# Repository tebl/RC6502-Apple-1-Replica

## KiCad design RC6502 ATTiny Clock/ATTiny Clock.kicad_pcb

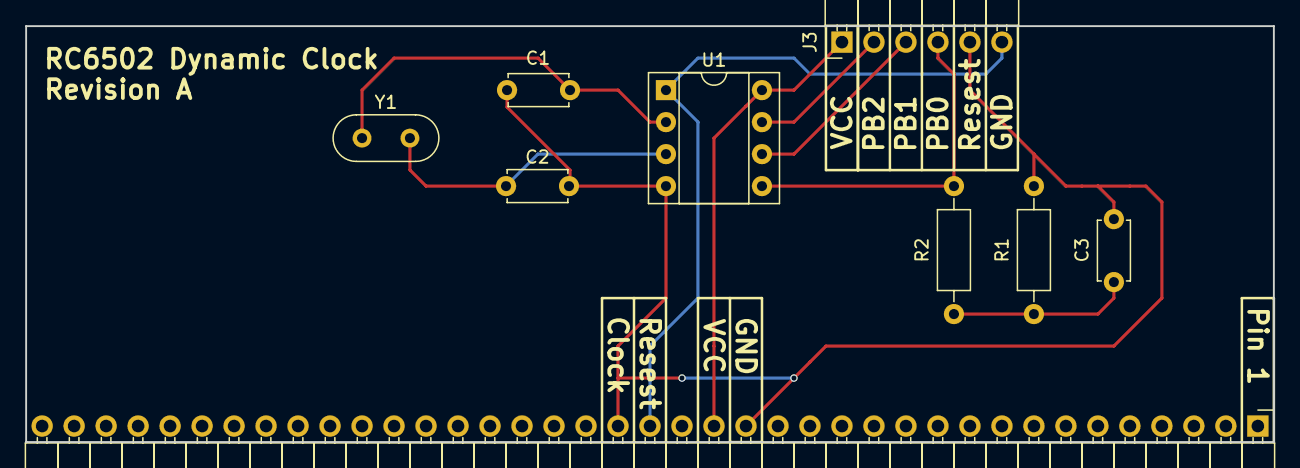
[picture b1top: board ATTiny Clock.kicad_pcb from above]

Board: 2 copper layers, 99.1 x 33.0 mm, 9 parts (0 on the bottom side), 9 nets.

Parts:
C1, C2: 22pF; C_Disc_D4.7mm_W2.5mm_P5.00mm
C3: 0.1uF; C_Disc_D4.7mm_W2.5mm_P5.00mm
J1: CONN_01X39; Pin_Header_Angled_1x39_Pitch2.54mm
J3: CONN_01X06; Pin_Header_Angled_1x06_Pitch2.54mm
R1: 10k; R_Axial_DIN0207_L6.3mm_D2.5mm_P10.16mm_Horizontal
R2: 1k; R_Axial_DIN0207_L6.3mm_D2.5mm_P10.16mm_Horizontal
U1: ATTINY85-20PU; DIP-8_W7.62mm_Socket
Y1: 20Mhz; Crystal_HC52-6mm_Vertical

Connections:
CLOCK: C1.2, C2.2, C3.2, J1.17, J1.21, J3.5, R1.2, U1.4
unnamed: C3.1, R1.1, R2.2
PB0: J3.4, R2.1, U1.5
PB1: J3.3, U1.6
PB2: J3.2, U1.7
RESET: J1.20, J3.6, U1.1
Vcc: J1.18, J3.1, U1.8
XTAL1: C1.1, U1.2, Y1.1
XTAL2: C2.1, U1.3, Y1.2

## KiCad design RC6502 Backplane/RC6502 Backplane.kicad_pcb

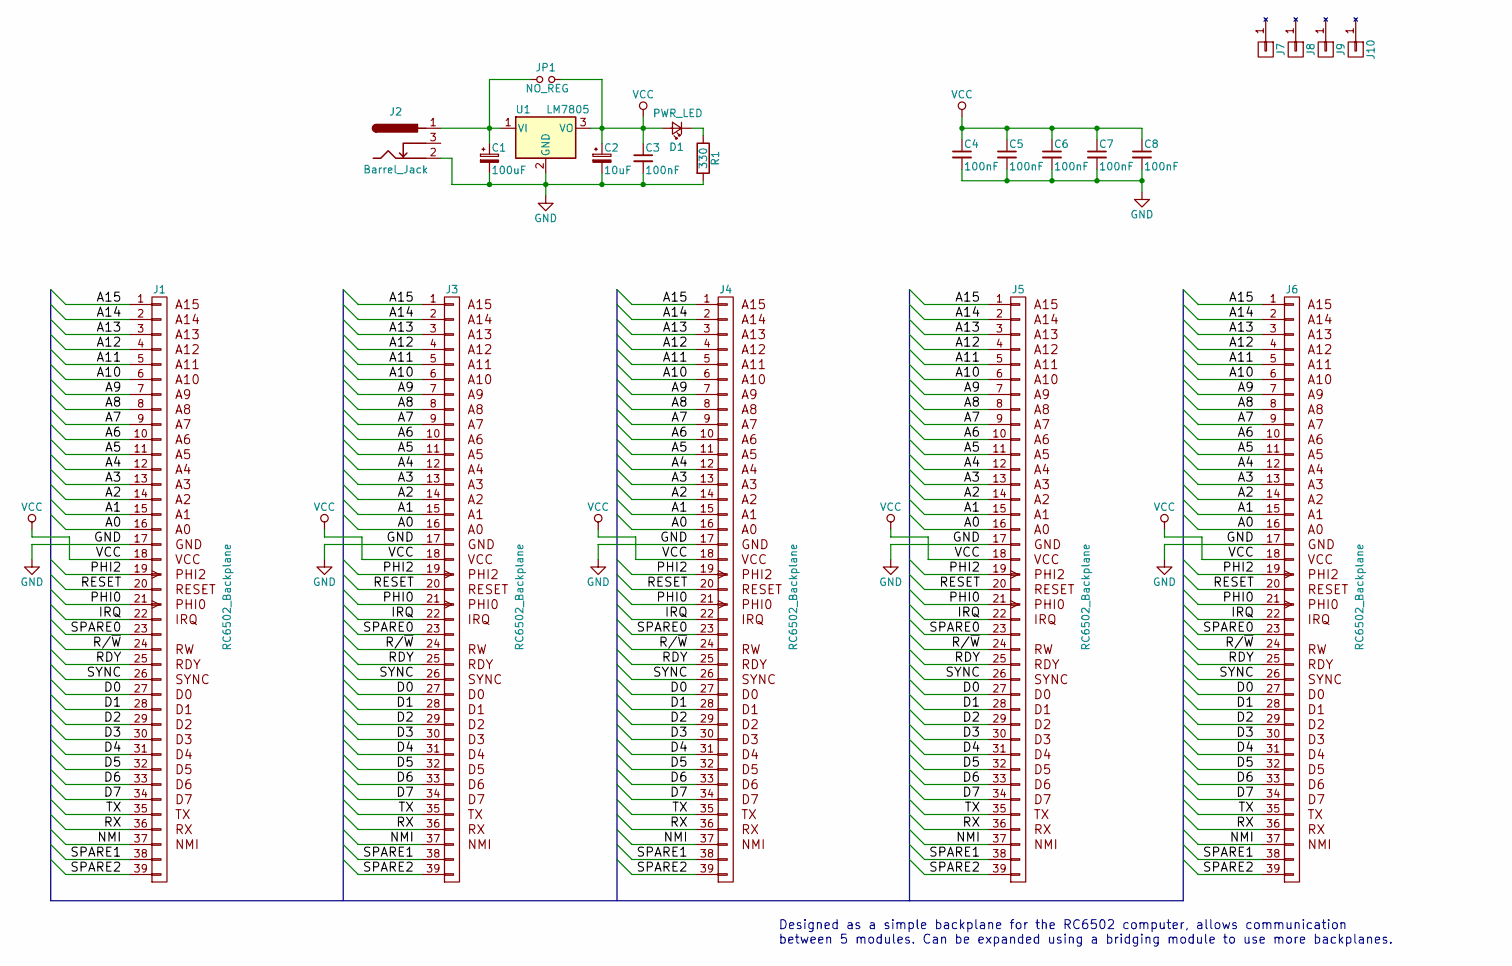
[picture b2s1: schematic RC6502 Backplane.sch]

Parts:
C1: 100uF; CP_Radial_D5.0mm_P2.50mm
C2: 10uF; CP_Radial_D4.0mm_P2.00mm
C3, C4, C5, C6, C7, C8: 100nF; C_Disc_D4.7mm_W2.5mm_P5.00mm
D1: PWR_LED; LED_D5.0mm
J1, J3, J4, J5, J6: RC6502_Backplane; Pin_Header_Straight_1x39_Pitch2.54mm
J2: Barrel_Jack; BARREL_JACK
J7, J8, J9, J10: Mounting
JP1: NO_REG; Pin_Header_Straight_1x02_Pitch2.54mm
R1: 330; R_Axial_DIN0207_L6.3mm_D2.5mm_P10.16mm_Horizontal
U1: LM7805; TO-220-3_Horizontal

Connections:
/A0: J1.16 (A0), J3.16 (A0), J4.16 (A0), J5.16 (A0), J6.16 (A0)
/A1: J1.15 (A1), J3.15 (A1), J4.15 (A1), J5.15 (A1), J6.15 (A1)
/A2: J1.14 (A2), J3.14 (A2), J4.14 (A2), J5.14 (A2), J6.14 (A2)
/A3: J1.13 (A3), J3.13 (A3), J4.13 (A3), J5.13 (A3), J6.13 (A3)
/A4: J1.12 (A4), J3.12 (A4), J4.12 (A4), J5.12 (A4), J6.12 (A4)
/A5: J1.11 (A5), J3.11 (A5), J4.11 (A5), J5.11 (A5), J6.11 (A5)
/A6: J1.10 (A6), J3.10 (A6), J4.10 (A6), J5.10 (A6), J6.10 (A6)
/A7: J1.9 (A7), J3.9 (A7), J4.9 (A7), J5.9 (A7), J6.9 (A7)
/A8: J1.8 (A8), J3.8 (A8), J4.8 (A8), J5.8 (A8), J6.8 (A8)
/A9: J1.7 (A9), J3.7 (A9), J4.7 (A9), J5.7 (A9), J6.7 (A9)
/A10: J1.6 (A10), J3.6 (A10), J4.6 (A10), J5.6 (A10), J6.6 (A10)
/A11: J1.5 (A11), J3.5 (A11), J4.5 (A11), J5.5 (A11), J6.5 (A11)
/A12: J1.4 (A12), J3.4 (A12), J4.4 (A12), J5.4 (A12), J6.4 (A12)
/A13: J1.3 (A13), J3.3 (A13), J4.3 (A13), J5.3 (A13), J6.3 (A13)
/A14: J1.2 (A14), J3.2 (A14), J4.2 (A14), J5.2 (A14), J6.2 (A14)
/A15: J1.1 (A15), J3.1 (A15), J4.1 (A15), J5.1 (A15), J6.1 (A15)
/D0: J1.27 (D0), J3.27 (D0), J4.27 (D0), J5.27 (D0), J6.27 (D0)
/D1: J1.28 (D1), J3.28 (D1), J4.28 (D1), J5.28 (D1), J6.28 (D1)
/D2: J1.29 (D2), J3.29 (D2), J4.29 (D2), J5.29 (D2), J6.29 (D2)
/D3: J1.30 (D3), J3.30 (D3), J4.30 (D3), J5.30 (D3), J6.30 (D3)
/D4: J1.31 (D4), J3.31 (D4), J4.31 (D4), J5.31 (D4), J6.31 (D4)
/D5: J1.32 (D5), J3.32 (D5), J4.32 (D5), J5.32 (D5), J6.32 (D5)
/D6: J1.33 (D6), J3.33 (D6), J4.33 (D6), J5.33 (D6), J6.33 (D6)
/D7: J1.34 (D7), J3.34 (D7), J4.34 (D7), J5.34 (D7), J6.34 (D7)
/IRQ: J1.22 (IRQ), J3.22 (IRQ), J4.22 (IRQ), J5.22 (IRQ), J6.22 (IRQ)
/NMI: J1.37 (NMI), J3.37 (NMI), J4.37 (NMI), J5.37 (NMI), J6.37 (NMI)
/PHI0: J1.21 (PHI0), J3.21 (PHI0), J4.21 (PHI0), J5.21 (PHI0), J6.21 (PHI0)
/PHI2: J1.19 (PHI2), J3.19 (PHI2), J4.19 (PHI2), J5.19 (PHI2), J6.19 (PHI2)
/R/~W: J1.24 (RW), J3.24 (RW), J4.24 (RW), J5.24 (RW), J6.24 (RW)
/RDY: J1.25 (READY), J3.25 (READY), J4.25 (READY), J5.25 (READY), J6.25 (READY)
/RESET: J1.20 (RESET), J3.20 (RESET), J4.20 (RESET), J5.20 (RESET), J6.20 (RESET)
/RX: J1.36 (RX), J3.36 (RX), J4.36 (RX), J5.36 (RX), J6.36 (RX)
/SPARE0: J1.23, J3.23, J4.23, J5.23, J6.23
/SPARE1: J1.38, J3.38, J4.38, J5.38, J6.38
/SPARE2: J1.39, J3.39, J4.39, J5.39, J6.39
/SYNC: J1.26 (SYNC), J3.26 (SYNC), J4.26 (SYNC), J5.26 (SYNC), J6.26 (SYNC)
/TX: J1.35 (TX), J3.35 (TX), J4.35 (TX), J5.35 (TX), J6.35 (TX)
GND: C1.2, C2.2, C3.2, C4.2, C5.2, C6.2, C7.2, C8.2, J1.17, J2.2, J3.17, J4.17, J5.17, J6.17, R1.2, U1.2 (GND)
unnamed: C1.1, J2.1, JP1.1, U1.1 (VI)
unnamed: D1.1 (K), R1.1
VCC: C2.1, C3.1, C4.1, C5.1, C6.1, C7.1, C8.1, D1.2 (A), J1.18, J3.18, J4.18, J5.18, J6.18, JP1.2, U1.3 (VO)

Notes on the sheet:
Designed as a simple backplane for the RC6502 computer, allows communication between 5 modules. Can be expanded using a bridging module to use more backplanes.

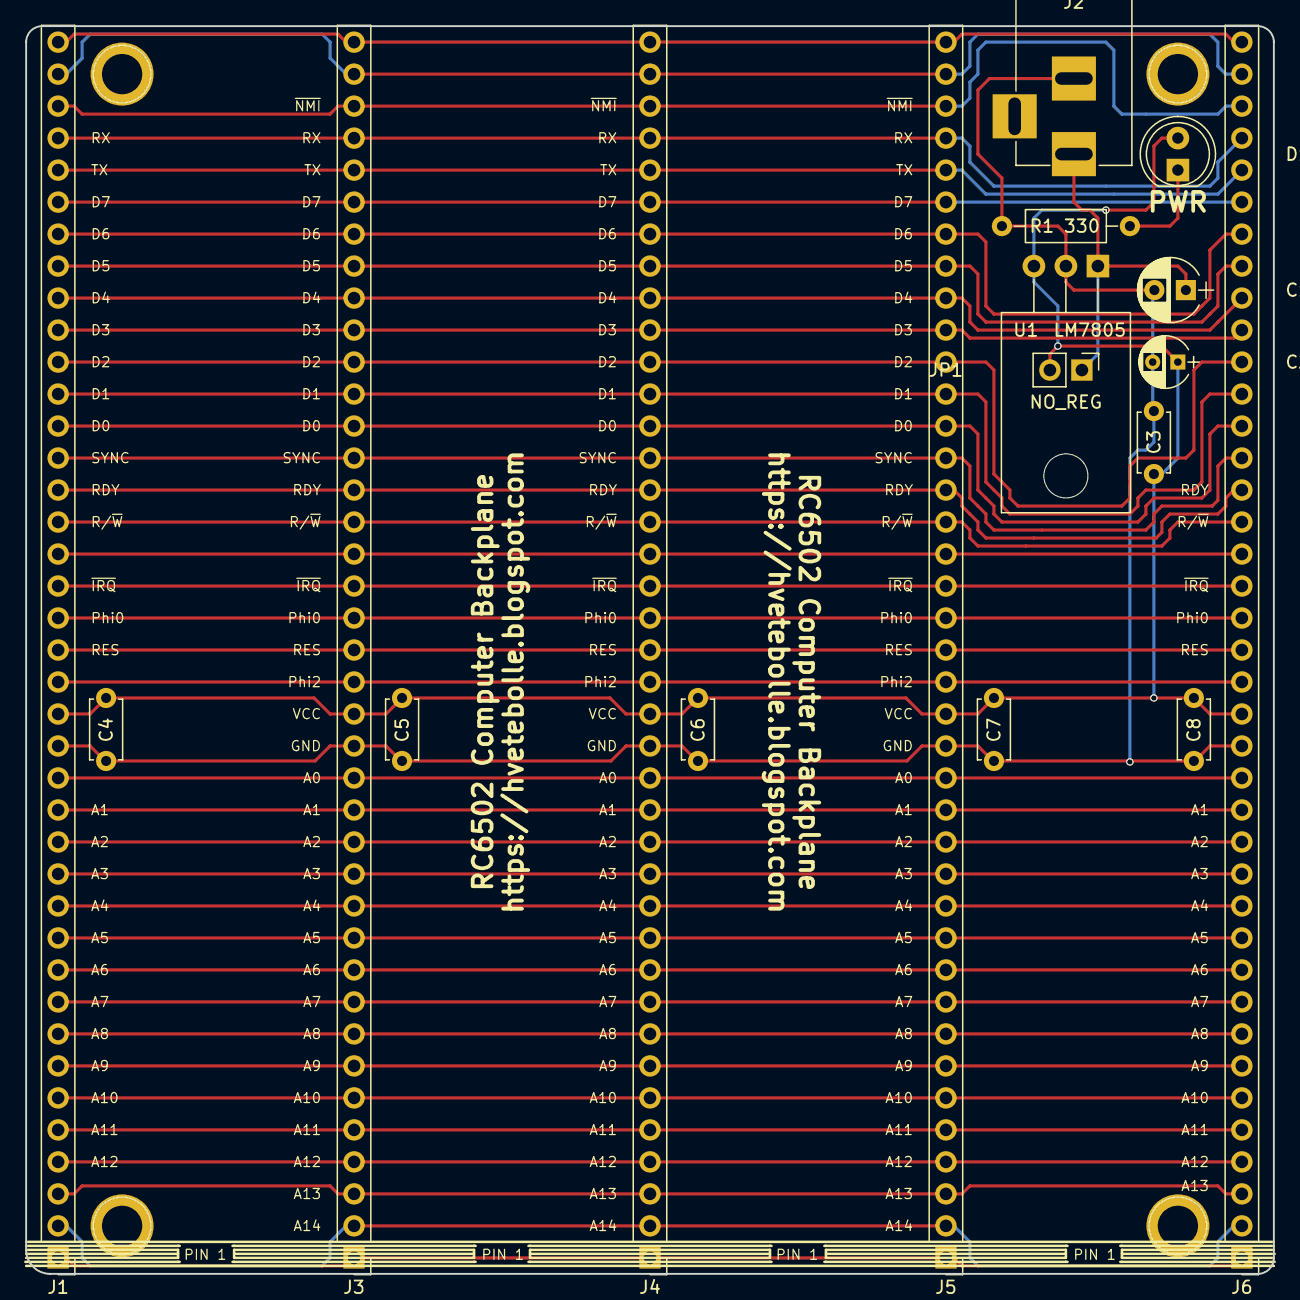
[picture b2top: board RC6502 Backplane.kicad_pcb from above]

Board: 2 copper layers, 99.1 x 99.1 mm, 22 parts (0 on the bottom side), 41 nets.

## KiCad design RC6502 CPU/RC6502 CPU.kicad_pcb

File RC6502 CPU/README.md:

# RC6502 CPU

Ah... The CPU-module (Central Processing Unit), definitely the brains of the operation! While the original sported an MOS-branded, the same company later bought out by Commodore and adapter for their computers, ceramic 6502 CPU the later clones available to us now haven't changed all that much. For that reason you can easily substitute the MOS-part with an easily obtainable UM6502 or an SY6502 without any changes, the newer and substantially changed W65C02 however remains incompatible at the moment.

The original computer ran at a blazing 1Mhz, but if you can find a 6502A you could probably crank this computer all the way up to 2Mhz! The speed the computer would run at (successfully or not) will be determined by the crystal oscillator, while it can be mounted onto the CPU-module and enabled by jumpering JP1/JP2 the logical place for this in a more modern configuration would be on the [Reset circuit](https://github.com/tebl/RC6502-Apple-1-Replica/tree/master/RC6502%20Reset%20Circuit)-module. The reason for including it here is simply that the original Apple 1 computer didn't have a power-on reset circuitry, but seriously - get one! If you have plans for building more than one CPU boards with varying speeds, it would make sense to keep these together on the same board so that you can easily swap between them.

Revision A of the board is shown below, the newer revisions have a more simplified design due to a separate RD-signal being dropped from later designs. This was originally intended to help compatibility with the RC2014 computer, but this idea was abandoned due to the required increase in complexity in order to support a handfull of builds.

# Schematic
The supplied KiCad files should be sufficient as both a schematic and as a starting
point for ordering PCBs, the schematic is also available in
[PDF-format](https://github.com/tebl/RC6502-Apple-1-Replica/raw/master/RC6502%20CPU/export/RC6502%20CPU.pdf). You can refer to the BOM below for a list of suggested components to use, part numbers in parenthesis are optional and is not required.

# BOM
These are the components needed to put together your very own ROM-module for the RC6502 computer, should be able to get all of this from your favourite parts supplier through your favourite local parts supplier. For the pin headers, both male and female - if you can't find the exact pin count, just buy the longer versions and snip/cut off the parts you don't need (get extra in case of accidents, and don't cut yourself either!). As previously mentioned, part counts in parenthesis are to be considered optional so feel free to leave them out if you don't have any specific plans for them.

| Reference | Item                                  | Count  |
| --------- | ------------------------------------- | ------ |
| PCB       | Fabricate yourself using KiCad files  |     1  |
| U1        | 6502 CPU DIP-40, UM6502 or SY6502     |     1  |
| J1        | 1x39 right angle pin header, male     |     1  |
| J2-J4     | 1x2 right angle pin header, male      |     3  |
| JP1,JP2   | 1x2 right angle pin header, male      |   (2)  |
| R1-R3     | 3K3 (3300) Ohm resistor               |     3  |
| C1        | 100nF ceramic capacitor               |     1  |
| X1        | 1.000Mhz TTL Oscillator, (DIP 14)     |    (1) |
|           | Jumper caps                           |    (5) |

If you would like to have a copy of one or more modules, what you'll need to do is zip up the contents of the export directory for each module and give that to your favourite PCB fabrication plant. Personally I prefer to use [PCBWay](https://www.pcbway.com/setinvite.aspx?inviteid=88707), each module has been designed to fit inside the 5$ dimensions. Use the link provided when signing up to support this project!

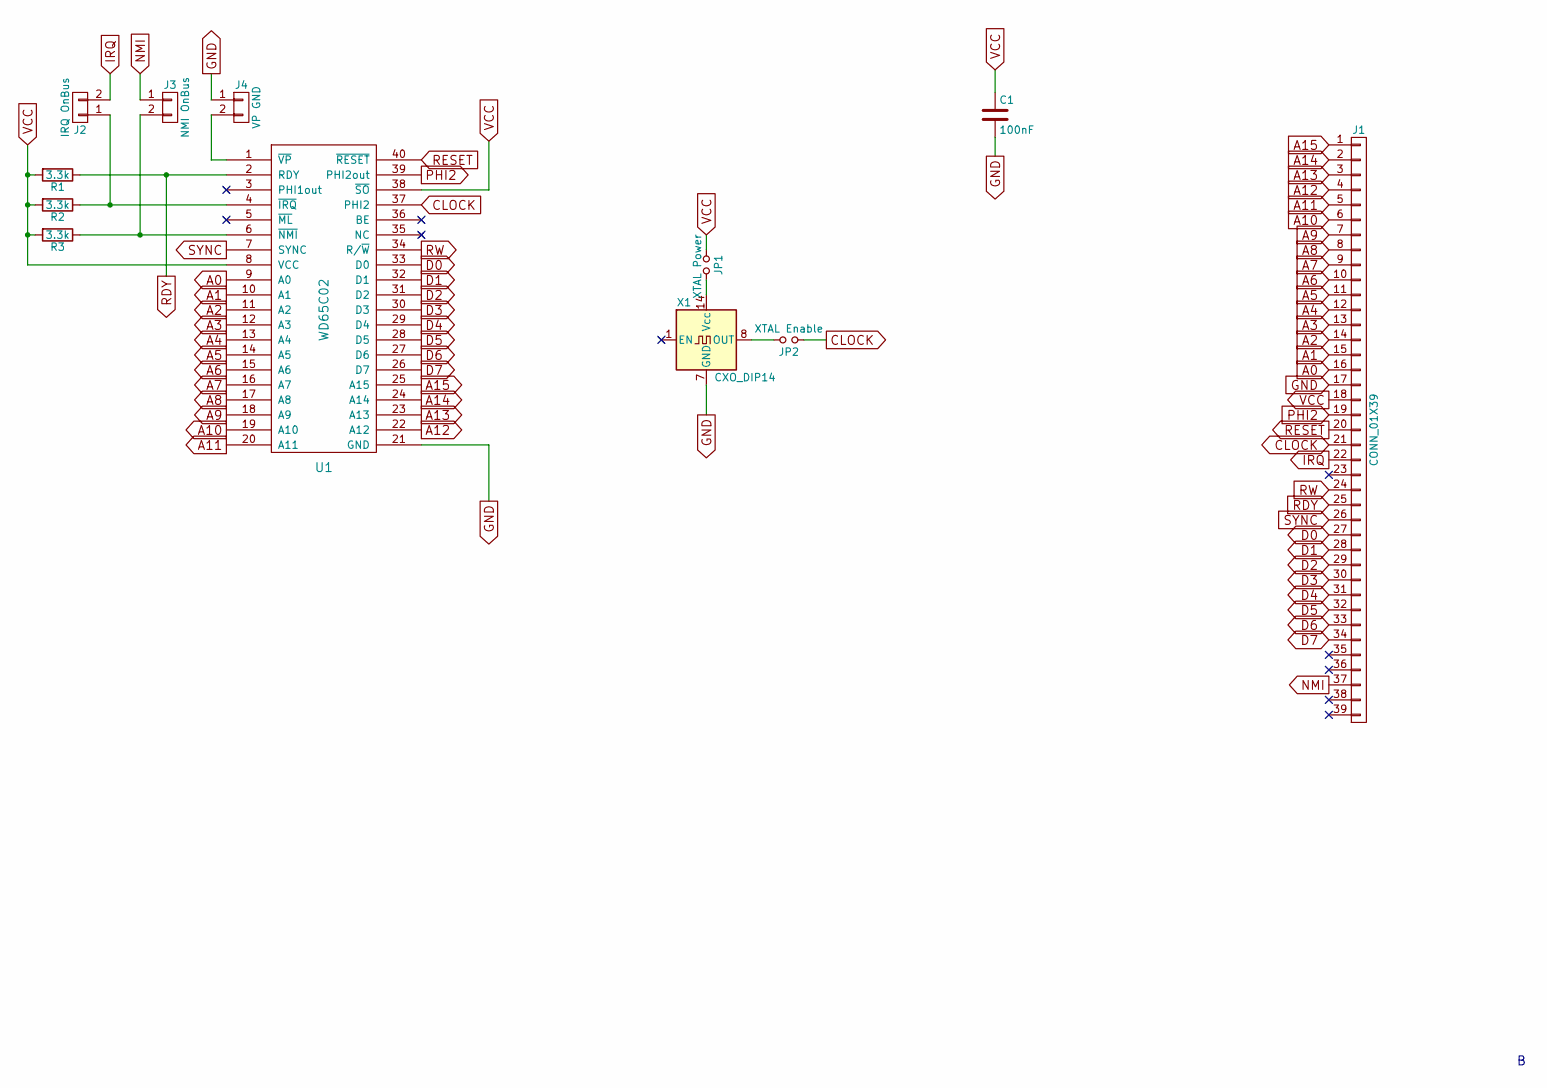
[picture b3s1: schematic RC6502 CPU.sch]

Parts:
C1: 100nF; C_Disc_D4.7mm_W2.5mm_P5.00mm
J1: CONN_01X39; Pin_Header_Angled_1x39_Pitch2.54mm
J2: IRQ OnBus; Pin_Header_Angled_1x02_Pitch2.54mm
J3: NMI OnBus; Pin_Header_Angled_1x02_Pitch2.54mm
J4: VP GND; Pin_Header_Angled_1x02_Pitch2.54mm
JP1: XTAL Power; Pin_Header_Angled_1x02_Pitch2.54mm
JP2: XTAL Enable; Pin_Header_Angled_1x02_Pitch2.54mm
R1, R2, R3: 3.3k; R_Axial_DIN0207_L6.3mm_D2.5mm_P10.16mm_Horizontal
U1: WD65C02; DIP-40_W15.24mm_Socket
X1: CXO_DIP14; Oscillator_DIP-14

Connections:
A0: J1.16, U1.9 (A0)
A1: J1.15, U1.10 (A1)
A2: J1.14, U1.11 (A2)
A3: J1.13, U1.12 (A3)
A4: J1.12, U1.13 (A4)
A5: J1.11, U1.14 (A5)
A6: J1.10, U1.15 (A6)
A7: J1.9, U1.16 (A7)
A8: J1.8, U1.17 (A8)
A9: J1.7, U1.18 (A9)
A10: J1.6, U1.19 (A10)
A11: J1.5, U1.20 (A11)
A12: J1.4, U1.22 (A12)
A13: J1.3, U1.23 (A13)
A14: J1.2, U1.24 (A14)
A15: J1.1, U1.25 (A15)
CLOCK: J1.21, JP2.1, U1.37 (PHI2)
D0: J1.27, U1.33 (D0)
D1: J1.28, U1.32 (D1)
D2: J1.29, U1.31 (D2)
D3: J1.30, U1.30 (D3)
D4: J1.31, U1.29 (D4)
D5: J1.32, U1.28 (D5)
D6: J1.33, U1.27 (D6)
D7: J1.34, U1.26 (D7)
GND: C1.2, J1.17, J4.1, U1.21 (GND), X1.7 (GND)
IRQ: J1.22, J2.2
NMI: J1.37, J3.1
unnamed: J2.1, R2.1, U1.4 (~IRQ)
unnamed: J3.2, R3.1, U1.6 (~NMI)
unnamed: J4.2, U1.1 (~VP)
unnamed: JP1.2, X1.14 (Vcc)
unnamed: JP2.2, X1.8 (OUT)
PHI2: J1.19, U1.39 (PHI2out)
RDY: J1.25, R1.1, U1.2 (RDY)
RESET: J1.20, U1.40 (~RESET)
RW: J1.24, U1.34 (R/~W)
SYNC: J1.26, U1.7 (SYNC)
VCC: C1.1, J1.18, JP1.1, R1.2, R2.2, R3.2, U1.8 (VCC), U1.38 (~SO)

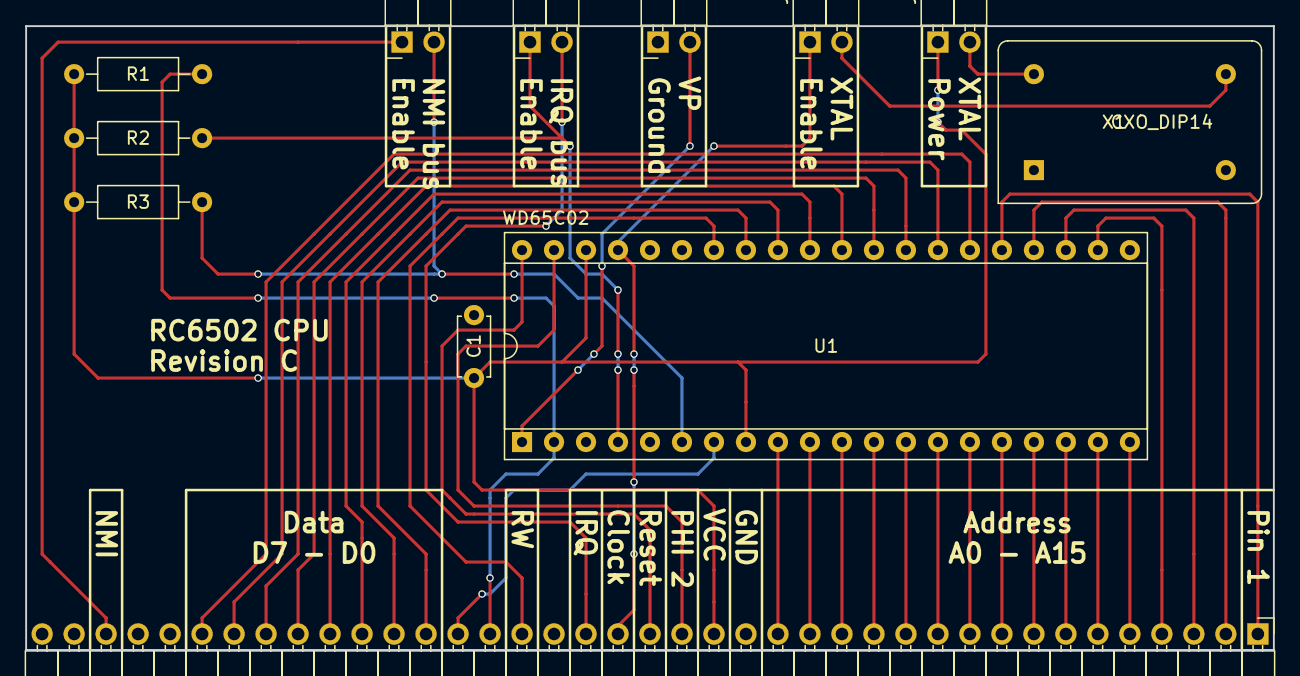
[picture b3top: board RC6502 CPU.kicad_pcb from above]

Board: 2 copper layers, 99.1 x 49.5 mm, 12 parts (0 on the bottom side), 39 nets.

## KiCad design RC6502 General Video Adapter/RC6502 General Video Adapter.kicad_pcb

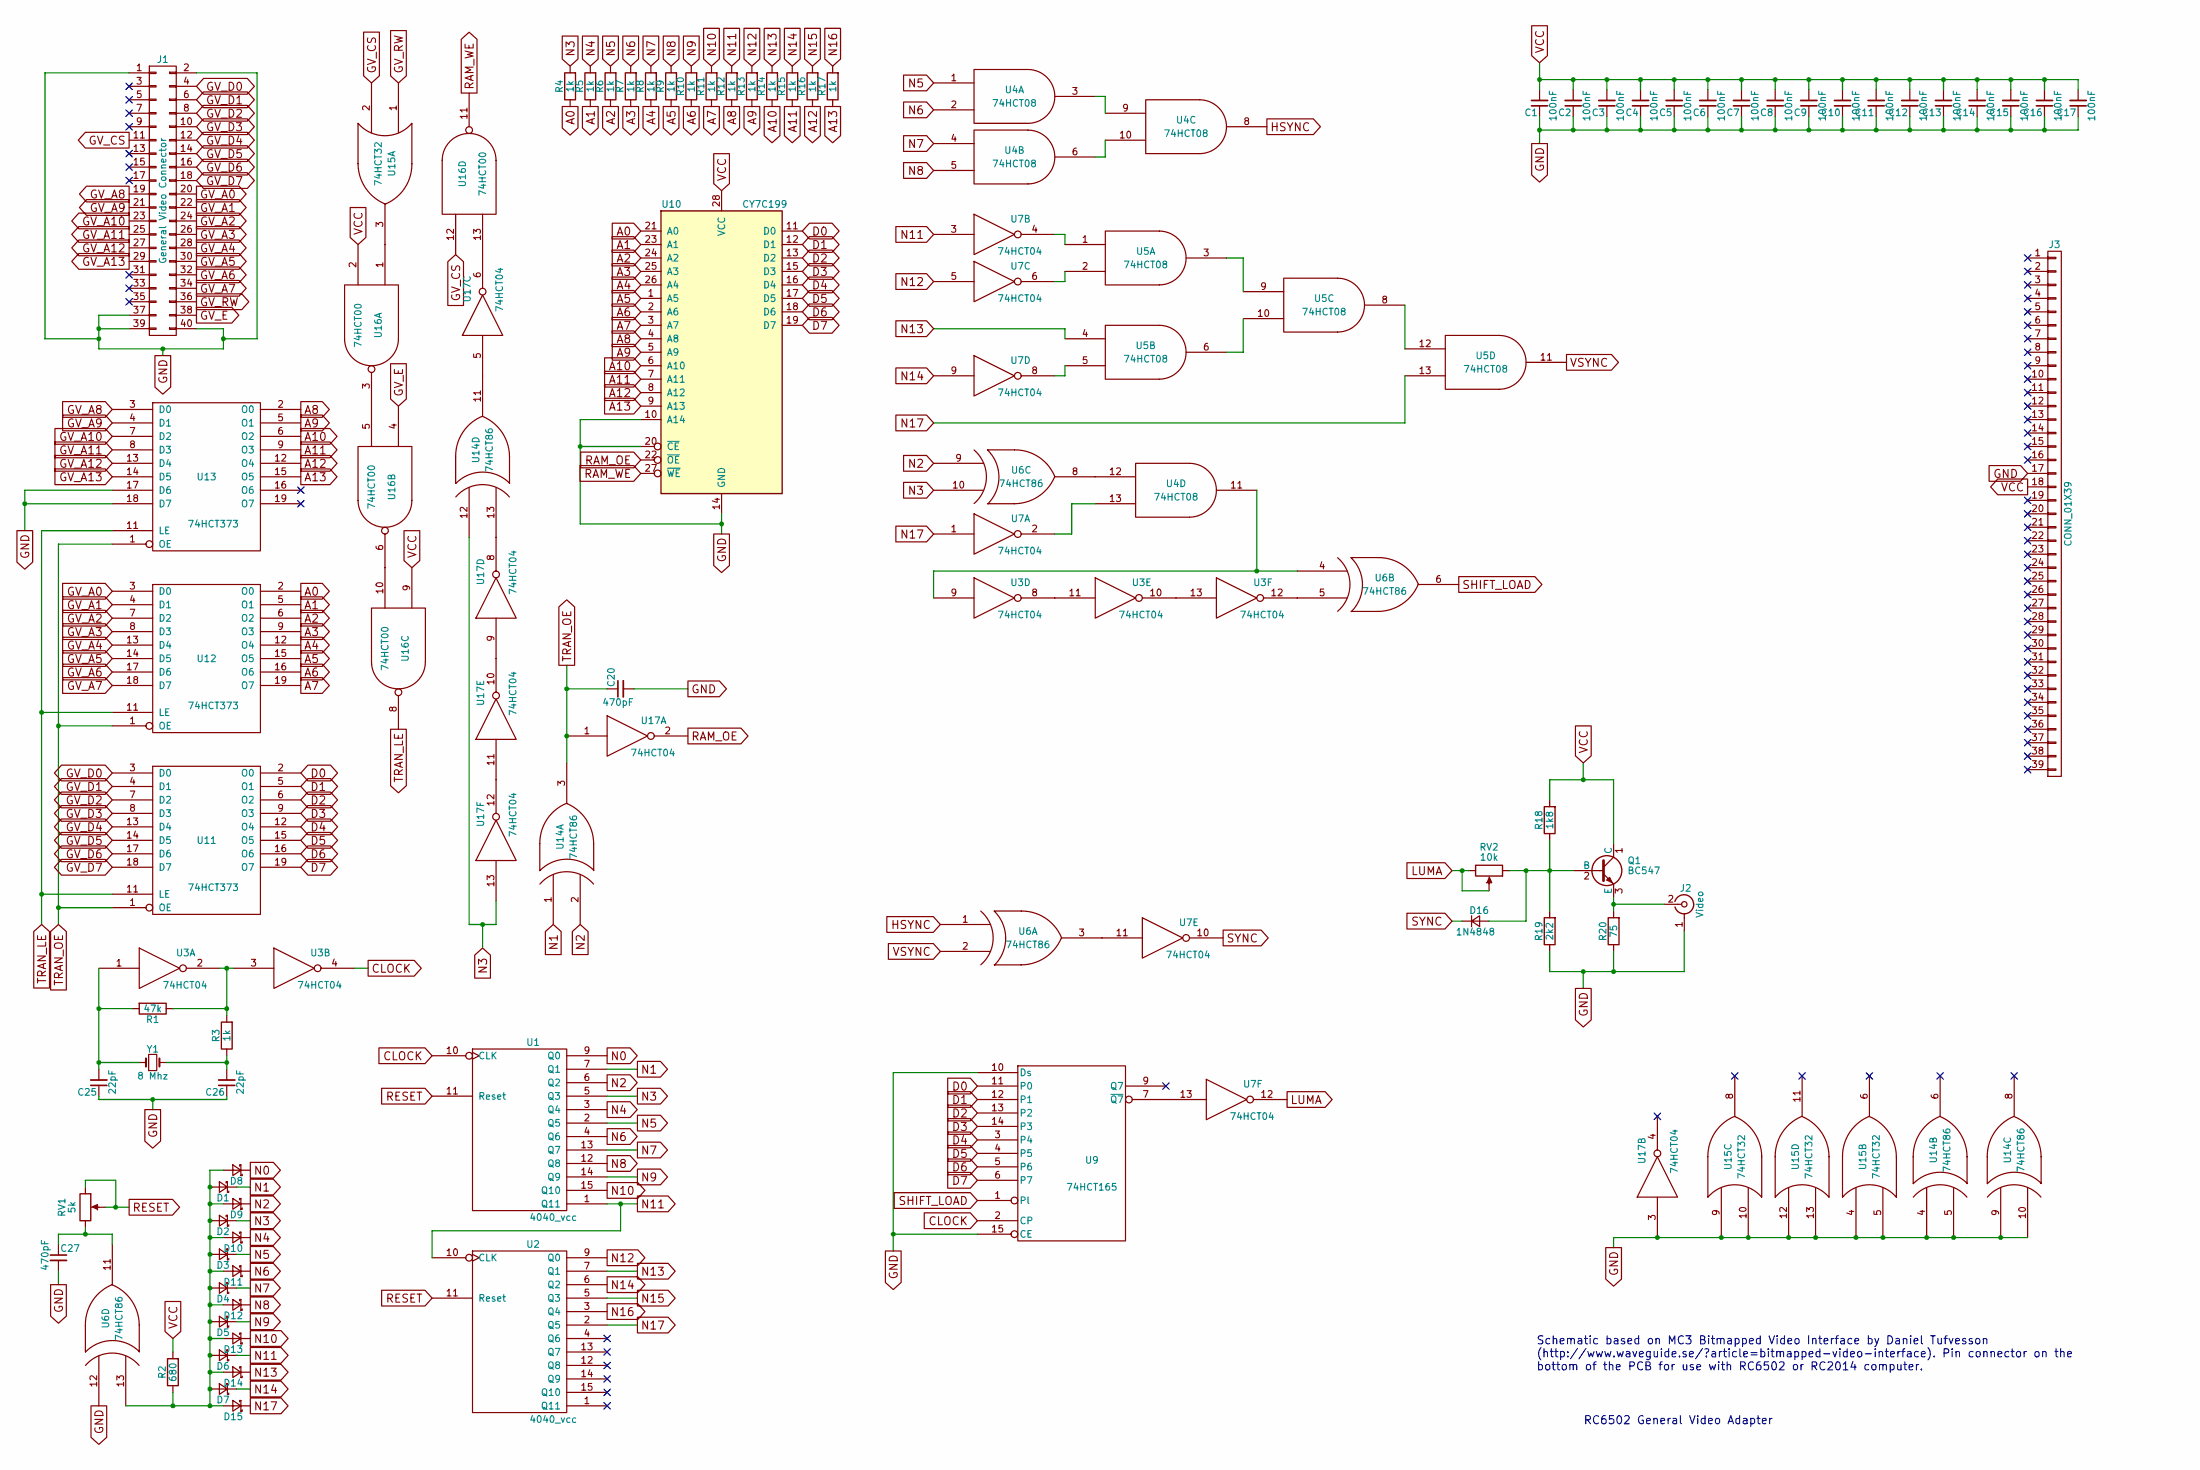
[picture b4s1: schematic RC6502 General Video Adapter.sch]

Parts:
C1, C2, C3, C4, C5, C6, C7, C8, C9, C10, C11, C12, C13, C14, C15, C16, C17: 100nF; C_Disc_D4.7mm_W2.5mm_P5.00mm
C20, C27: 470pF; C_Disc_D4.7mm_W2.5mm_P5.00mm
C25, C26: 22pF; C_Disc_D4.7mm_W2.5mm_P5.00mm
D1, D2, D3, D4, D5, D6, D7, D8, D9, D10, D11, D12, D13, D14, D15: BAT42; D_DO-35_SOD27_P7.62mm_Horizontal
D16: 1N4848; D_DO-35_SOD27_P7.62mm_Horizontal
J1: General Video Connector; IDC_Header_Straight_40pins
J2: Video; rca_yellow
J3: CONN_01X39; Pin_Header_Angled_1x39_Pitch2.54mm
Q1: BC547; TO-92_Molded_Narrow
R1: 47k; R_Axial_DIN0207_L6.3mm_D2.5mm_P10.16mm_Horizontal
R2: 680; R_Axial_DIN0207_L6.3mm_D2.5mm_P10.16mm_Horizontal
R3, R4, R5, R6, R7, R8, R9, R10, R11, R12, R13, R14, R15, R16, R17: 1k; R_Axial_DIN0207_L6.3mm_D2.5mm_P10.16mm_Horizontal
R18: 1k8; R_Axial_DIN0207_L6.3mm_D2.5mm_P10.16mm_Horizontal
R19: 2k2; R_Axial_DIN0207_L6.3mm_D2.5mm_P10.16mm_Horizontal
R20: 75; R_Axial_DIN0207_L6.3mm_D2.5mm_P10.16mm_Horizontal
RV1: 5k; Potentiometer_Trimmer_Bourns_3296W
RV2: 10k; Potentiometer_Trimmer_Bourns_3296W
U1, U2: 4040_vcc; DIP-16_W7.62mm_Socket
U3, U7, U17: 74HCT04; DIP-14_W7.62mm_Socket
U4, U5: 74HCT08; DIP-14_W7.62mm_Socket
U6, U14: 74HCT86; DIP-14_W7.62mm_Socket
U9: 74HCT165; DIP-16_W7.62mm_Socket
U10: CY7C199; DIP-28_W7.62mm_Socket
U11, U12, U13: 74HCT373; DIP-20_W7.62mm_Socket
U15: 74HCT32; DIP-14_W7.62mm_Socket
U16: 74HCT00; DIP-14_W7.62mm_Socket
Y1: 8 Mhz; Crystal_HC49-4H_Vertical

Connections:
A0: R4.1, U10.21 (A0), U12.2 (O0)
A1: R5.1, U10.23 (A1), U12.5 (O1)
A2: R6.1, U10.24 (A2), U12.6 (O2)
A3: R7.1, U10.25 (A3), U12.9 (O3)
A4: R8.1, U10.26 (A4), U12.12 (O4)
A5: R9.1, U10.1 (A5), U12.15 (O5)
A6: R10.1, U10.2 (A6), U12.16 (O6)
A7: R11.1, U10.3 (A7), U12.19 (O7)
A8: R12.1, U10.4 (A8), U13.2 (O0)
A9: R13.1, U10.5 (A9), U13.5 (O1)
A10: R14.1, U10.6 (A10), U13.6 (O2)
A11: R15.1, U10.7 (A11), U13.9 (O3)
A12: R16.1, U10.8 (A12), U13.12 (O4)
A13: R17.1, U10.9 (A13), U13.15 (O5)
CLOCK: U1.10 (CLK), U3.4, U9.2 (CP)
D0: U9.11 (P0), U10.11 (D0), U11.2 (O0)
D1: U9.12 (P1), U10.12 (D1), U11.5 (O1)
D2: U9.13 (P2), U10.13 (D2), U11.6 (O2)
D3: U9.14 (P3), U10.15 (D3), U11.9 (O3)
D4: U9.3 (P4), U10.16 (D4), U11.12 (O4)
D5: U9.4 (P5), U10.17 (D5), U11.15 (O5)
D6: U9.5 (P6), U10.18 (D6), U11.16 (O6)
D7: U9.6 (P7), U10.19 (D7), U11.19 (O7)
GND: C1.1, C2.1, C3.1, C4.1, C5.1, C6.1, C7.1, C8.1, C9.1, C10.1, C11.1, C12.1, C13.1, C14.1, C15.1, C16.1, C17.1, C20.2, C25.1, C26.1, C27.2, J1.1, J1.2, J1.37, J1.39, J1.40, J2.1 (Ext), J3.17, R19.1, R20.1, U1.8 (GND), U2.8 (GND), U3.7 (GND), U4.7 (GND), U5.7 (GND), U6.7 (GND), U6.12 (IN1), U7.7 (GND), U9.8 (GND), U9.10 (Ds), U9.15 (CE), U10.10 (A14), U10.14 (GND), U10.20 (~CE~), U11.10 (GND), U12.10 (GND), U13.10 (GND), U13.17 (D6), U13.18 (D7), U14.4 (IN1), U14.5 (IN2), U14.7 (GND), U14.9 (IN1), U14.10 (IN2), U15.4, U15.5, U15.7 (GND), U15.9, U15.10, U15.12, U15.13, U16.7 (GND), U17.3, U17.7 (GND)
GV_A0: J1.20, U12.3 (D0)
GV_A1: J1.22, U12.4 (D1)
GV_A2: J1.24, U12.7 (D2)
GV_A3: J1.26, U12.8 (D3)
GV_A4: J1.28, U12.13 (D4)
GV_A5: J1.30, U12.14 (D5)
GV_A6: J1.32, U12.17 (D6)
GV_A7: J1.34, U12.18 (D7)
GV_A8: J1.19, U13.3 (D0)
GV_A9: J1.21, U13.4 (D1)
GV_A10: J1.23, U13.7 (D2)
GV_A11: J1.25, U13.8 (D3)
GV_A12: J1.27, U13.13 (D4)
GV_A13: J1.29, U13.14 (D5)
GV_CS: J1.11, U15.2, U16.12
GV_D0: J1.4, U11.3 (D0)
GV_D1: J1.6, U11.4 (D1)
GV_D2: J1.8, U11.7 (D2)
GV_D3: J1.10, U11.8 (D3)
GV_D4: J1.12, U11.13 (D4)
GV_D5: J1.14, U11.14 (D5)
GV_D6: J1.16, U11.17 (D6)
GV_D7: J1.18, U11.18 (D7)
GV_E: J1.38, U16.4
GV_RW: J1.36, U15.1
HSYNC: U4.8, U6.1 (IN1)
LUMA: RV2.2, RV2.3, U7.12
N0: D8.1 (K), U1.9 (Q0)
N1: D1.1 (K), U1.7 (Q1), U14.1 (IN1)
N2: D9.1 (K), U1.6 (Q2), U6.9 (IN1), U14.2 (IN2)
N3: D2.1 (K), R4.2, U1.5 (Q3), U6.10 (IN2), U14.12 (IN1), U17.13
N4: D10.1 (K), R5.2, U1.3 (Q4)
N5: D3.1 (K), R6.2, U1.2 (Q5), U4.1
N6: D11.1 (K), R7.2, U1.4 (Q6), U4.2
N7: D4.1 (K), R8.2, U1.13 (Q7), U4.4
N8: D12.1 (K), R9.2, U1.12 (Q8), U4.5
N9: D5.1 (K), R10.2, U1.14 (Q9)
N10: D13.1 (K), R11.2, U1.15 (Q10)
N11: D6.1 (K), R12.2, U1.1 (Q11), U2.10 (CLK), U7.3
N12: R13.2, U2.9 (Q0), U7.5
N13: D14.1 (K), R14.2, U2.7 (Q1), U5.4
N14: D7.1 (K), R15.2, U2.6 (Q2), U7.9
N15: R16.2, U2.5 (Q3)
N16: R17.2, U2.3 (Q4)
N17: D15.1 (K), U2.2 (Q5), U5.13, U7.1
unnamed: C25.2, R1.2, U3.1, Y1.1
unnamed: C26.2, R3.1, Y1.2
unnamed: C27.1, RV1.3, U6.11 (OUT)
unnamed: D1.2 (A), D2.2 (A), D3.2 (A), D4.2 (A), D5.2 (A), D6.2 (A), D7.2 (A), D8.2 (A), D9.2 (A), D10.2 (A), D11.2 (A), D12.2 (A), D13.2 (A), D14.2 (A), D15.2 (A), R2.1, U6.13 (IN2)
unnamed: D16.2 (A), Q1.2 (B), R18.1, R19.2, RV2.1
unnamed: J2.2 (In), Q1.3 (E), R20.2
unnamed: R1.1, R3.2, U3.2, U3.3
unnamed: U3.9, U4.11, U6.4 (IN1)
unnamed: U3.10, U3.13
unnamed: U3.8, U3.11
unnamed: U3.12, U6.5 (IN2)
unnamed: U4.3, U4.9
unnamed: U4.6, U4.10
unnamed: U4.12, U6.8 (OUT)
unnamed: U4.13, U7.2
unnamed: U5.1, U7.4
unnamed: U5.2, U7.6
unnamed: U5.3, U5.9
unnamed: U5.5, U7.8
unnamed: U5.6, U5.10
unnamed: U5.8, U5.12
unnamed: U6.3 (OUT), U7.11
unnamed: U7.13, U9.7 (~Q7)
unnamed: U14.11 (OUT), U17.5
unnamed: U14.13 (IN2), U17.8
unnamed: U15.3, U16.1
unnamed: U16.3, U16.5
unnamed: U16.6, U16.10
unnamed: U16.13, U17.6
unnamed: U17.9, U17.10
unnamed: U17.11, U17.12
RAM_OE: U10.22 (~OE~), U17.2
RAM_WE: U10.27 (~WE~), U16.11
RESET: RV1.1, RV1.2, U1.11 (Reset), U2.11 (Reset)
SHIFT_LOAD: U6.6 (OUT), U9.1 (Pl)
SYNC: D16.1 (K), U7.10
TRAN_LE: U11.11 (LE), U12.11 (LE), U13.11 (LE), U16.8
TRAN_OE: C20.1, U11.1 (OE), U12.1 (OE), U13.1 (OE), U14.3 (OUT), U17.1
VCC: C1.2, C2.2, C3.2, C4.2, C5.2, C6.2, C7.2, C8.2, C9.2, C10.2, C11.2, C12.2, C13.2, C14.2, C15.2, C16.2, C17.2, J3.18, Q1.1 (C), R2.2, R18.2, U1.16 (VCC), U2.16 (VCC), U3.14 (VCC), U4.14 (VCC), U5.14 (VCC), U6.14 (VCC), U7.14 (VCC), U9.16 (VCC), U10.28 (VCC), U11.20 (VCC), U12.20 (VCC), U13.20 (VCC), U14.14 (VCC), U15.14 (VCC), U16.2, U16.9, U16.14 (VCC), U17.14 (VCC)
VSYNC: U5.11, U6.2 (IN2)

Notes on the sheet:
Schematic based on MC3 Bitmapped Video Interface by Daniel Tufvesson (http://www.waveguide.se/?article=bitmapped-video-interface). Pin connector on the bottom of the PCB for use with RC6502 or RC2014 computer.
RC6502 General Video Adapter

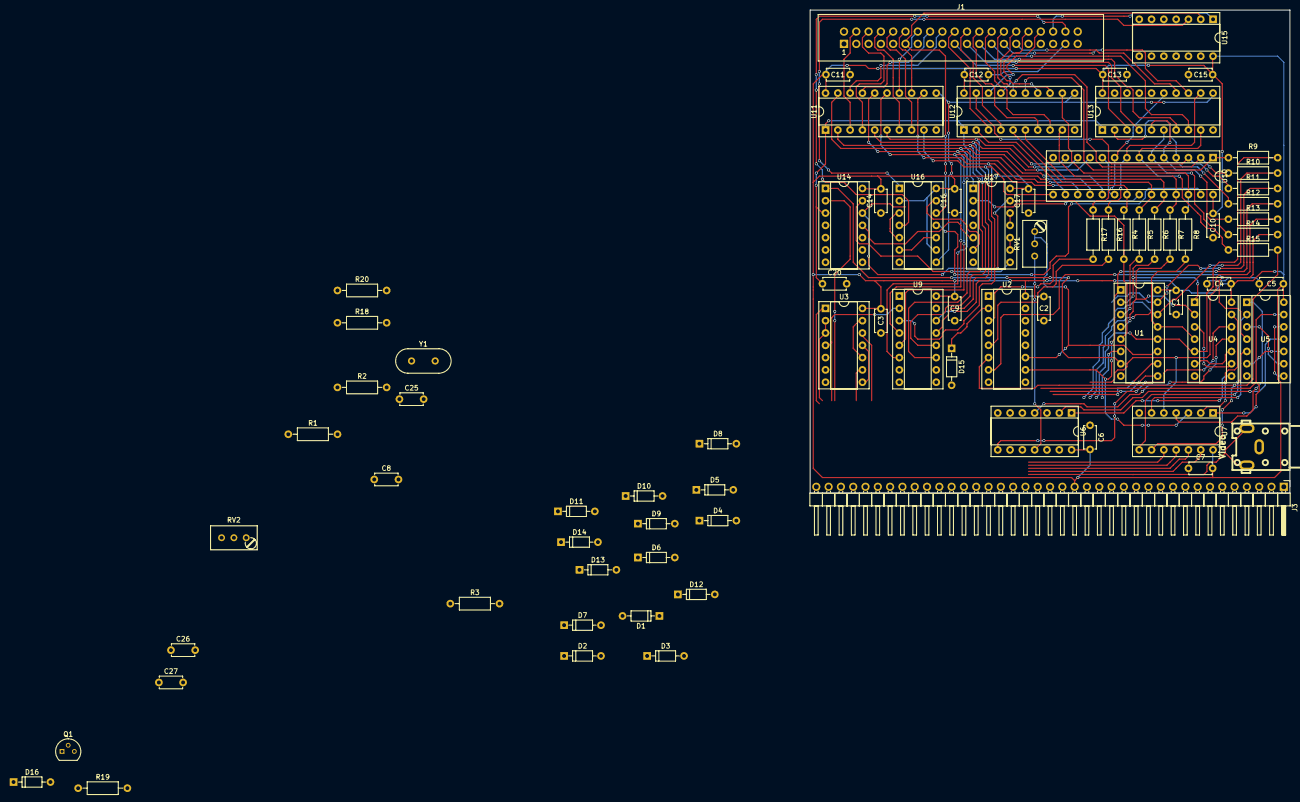
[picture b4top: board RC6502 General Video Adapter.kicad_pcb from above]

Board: 2 copper layers, 99.1 x 99.7 mm, 80 parts (0 on the bottom side), 109 nets.
